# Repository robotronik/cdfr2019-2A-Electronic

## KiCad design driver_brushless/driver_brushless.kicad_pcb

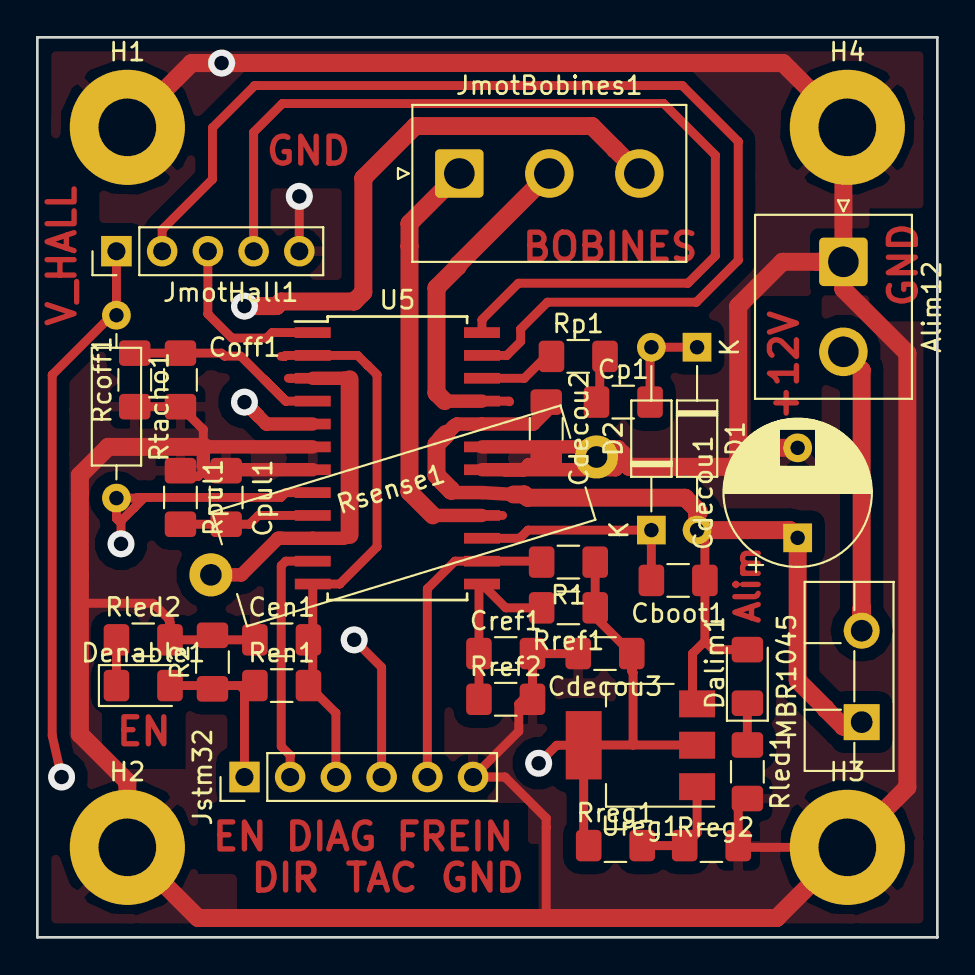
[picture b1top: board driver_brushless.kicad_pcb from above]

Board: 2 copper layers, 50.0 x 50.0 mm, 38 parts (0 on the bottom side), 26 nets.

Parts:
Alim12: B_Plug_5mm; JST_NV_B02P-NV_1x02_P5.00mm_Vertical
Cboot1: 220n; C_1206_3216Metric_Pad1.42x1.75mm_HandSolder
Cdecou1: 100µF; CP_Radial_D8.0mm_P5.00mm
Cdecou2, Cdecou3: 100nF; C_1206_3216Metric_Pad1.42x1.75mm_HandSolder
Cen1: 5.6n; C_1206_3216Metric_Pad1.42x1.75mm_HandSolder
Coff1: 1n; C_1206_3216Metric_Pad1.42x1.75mm_HandSolder
Cp1: 10n; C_1206_3216Metric_Pad1.42x1.75mm_HandSolder
Cpul1: 10n; C_1206_3216Metric_Pad1.42x1.75mm_HandSolder
Cref1: 10n; C_1206_3216Metric_Pad1.42x1.75mm_HandSolder
D1, D2: 1N4148; D_DO-35_SOD27_P10.16mm_Horizontal
Dalim1: LED; LED_1206_3216Metric_Pad1.42x1.75mm_HandSolder
Denable1: LED; LED_1206_3216Metric_Pad1.42x1.75mm_HandSolder
H1, H2, H3, H4: MountingHole_Pad; MountingHole_3.2mm_M3_Pad
JmotBobines1: Conn_01x03_Female; JST_NV_B03P-NV_1x03_P5.00mm_Vertical
JmotHall1: Conn_01x05_Female; PinHeader_1x05_P2.54mm_Vertical
Jstm32: Conn_01x06_Male; PinHeader_1x06_P2.54mm_Vertical
MBR1045: D_Schottky; TO-220F-2_Vertical
R1, R2: 100k; R_1206_3216Metric_Pad1.42x1.75mm_HandSolder
Rcoff1: 33k; R_1206_3216Metric_Pad1.42x1.75mm_HandSolder
Ren1: 100k; R_1206_3216Metric_Pad1.42x1.75mm_HandSolder
Rled1: 2,2k; R_1206_3216Metric_Pad1.42x1.75mm_HandSolder
Rled2: 680; R_1206_3216Metric_Pad1.42x1.75mm_HandSolder
Rp1: 100; R_1206_3216Metric_Pad1.42x1.75mm_HandSolder
Rpul1: 47k; R_1206_3216Metric_Pad1.42x1.75mm_HandSolder
Rref1: 1.2k; R_1206_3216Metric_Pad1.42x1.75mm_HandSolder
Rref2: 220; R_1206_3216Metric_Pad1.42x1.75mm_HandSolder
Rreg1: 270; R_1206_3216Metric_Pad1.42x1.75mm_HandSolder
Rreg2: 820; R_1206_3216Metric_Pad1.42x1.75mm_HandSolder
Rsense1: 0.3; R_Axial_Power_L20.0mm_W6.4mm_P22.40mm
Rtacho1: 1k; R_Axial_DIN0207_L6.3mm_D2.5mm_P10.16mm_Horizontal
U5: L6235D; SOIC-24W_7.5x15.4mm_P1.27mm
Ureg1: LM317; SOT-223-3_TabPin2

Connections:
+5V: Cdecou3.1, JmotHall1.1, R1.1, Rref1.1, Rreg1.1, Rtacho1.1, Ureg1.2
+12V: Cboot1.1, Cdecou1.1, Cdecou2.1, D1.2, Dalim1.2, MBR1045.1, U5.17, U5.20, Ureg1.3
/Hall_sensor_11: JmotHall1.3, U5.1
/Hall_sensor_21: JmotHall1.2, U5.23
/Hall_sensor_31: JmotHall1.4, U5.24
/Out_11: JmotBobines1.3, U5.5
/Out_21: JmotBobines1.2, U5.21
/Out_31: JmotBobines1.1, U5.16
GND: Alim12.1, Cdecou1.2, Cdecou2.2, Cdecou3.2, Cen1.1, Coff1.1, Cpul1.1, Cref1.2, H1.1, H2.1, H3.1, H4.1, JmotHall1.5, Jstm32.6, R2.2, Rcoff1.1, Rled1.2, Rled2.2, Rpul1.1, Rref2.2, Rreg2.2, Rsense1.2, U5.6, U5.7, U5.18, U5.19
unnamed: Alim12.2, MBR1045.2
unnamed: Cboot1.2, D2.1, U5.15
unnamed: Cen1.2, Jstm32.3, Ren1.2, U5.2, U5.12
unnamed: Coff1.2, Rcoff1.2, U5.4
unnamed: Cp1.1, Rp1.2
unnamed: Cp1.2, D1.1, D2.2
unnamed: Cpul1.2, Rpul1.2, U5.9
unnamed: Cref1.1, Rref1.2, Rref2.1, U5.13
unnamed: Dalim1.1, Rled1.1
unnamed: Denable1.1, Rled2.1
unnamed: Denable1.2, Jstm32.1, R2.1, Ren1.1
unnamed: Jstm32.2, U5.11
unnamed: Jstm32.4, Rtacho1.2, U5.8
unnamed: Jstm32.5, R1.2, U5.14
unnamed: Rp1.1, U5.22
unnamed: Rreg1.2, Rreg2.1, Ureg1.1
unnamed: Rsense1.1, U5.3, U5.10

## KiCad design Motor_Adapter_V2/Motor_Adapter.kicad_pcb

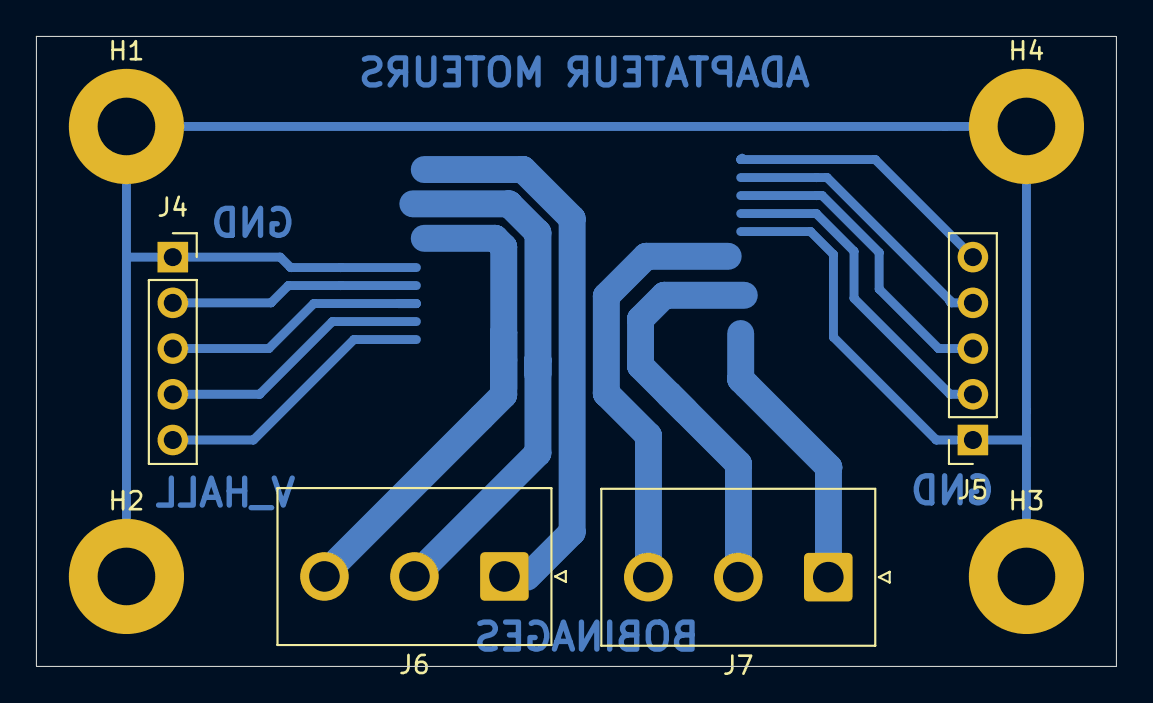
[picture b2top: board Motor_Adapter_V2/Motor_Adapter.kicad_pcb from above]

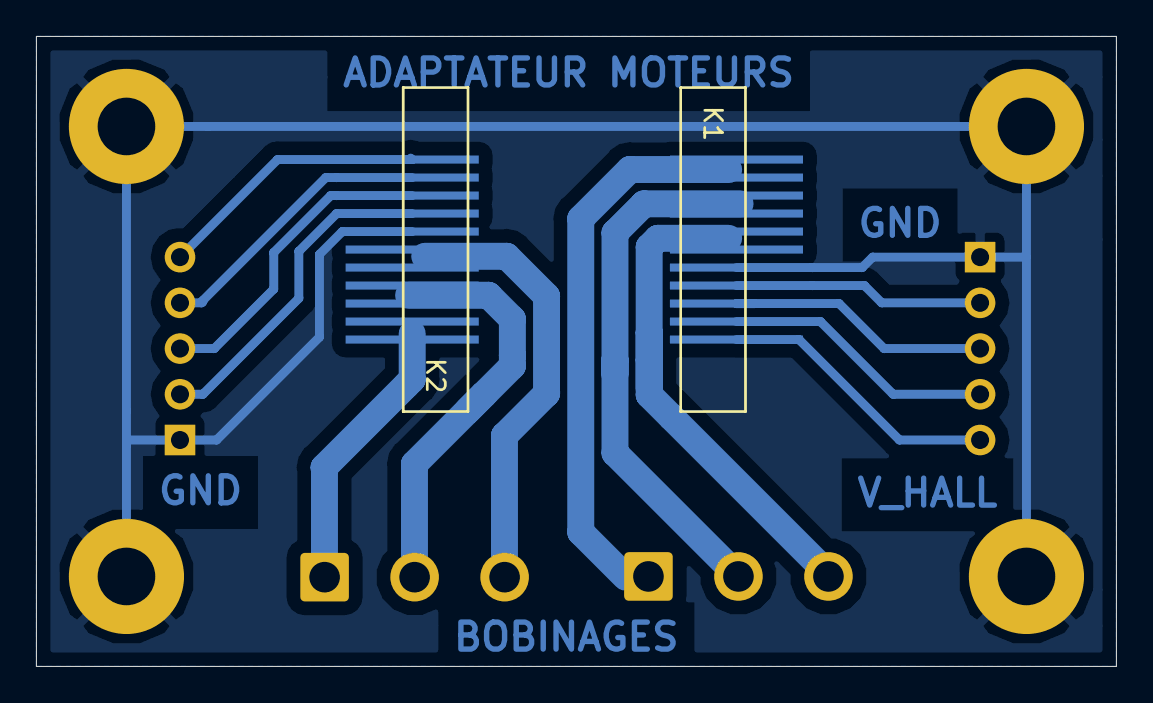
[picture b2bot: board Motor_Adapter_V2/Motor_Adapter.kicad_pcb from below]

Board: 2 copper layers, 60.0 x 35.0 mm, 10 parts (2 on the bottom side), 15 nets.

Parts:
H1, H2, H3, H4: MountingHole_Pad; MountingHole_3.2mm_M3_Pad
J4, J5: Hall_Sensor; PinSocket_1x05_P2.54mm_Vertical
J6, J7: Conn_01x03_Female; JST_NV_B03P-NV_1x03_P5.00mm_Vertical
K1, K2: Maxon-200142; Molex-52610-1133

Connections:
GND: H1.1, H2.1, H3.1, H4.1, J4.1, J5.1, K1.7, K2.7
unnamed: J4.2, K1.8
unnamed: J4.3, K1.9
unnamed: J4.4, K1.10
unnamed: J4.5, K1.11
unnamed: J5.2, K2.8
unnamed: J5.3, K2.9
unnamed: J5.4, K2.10
unnamed: J5.5, K2.11
unnamed: J6.1, K1.1, K1.2
unnamed: J6.2, K1.3, K1.4
unnamed: J6.3, K1.5, K1.6
unnamed: J7.1, K2.1, K2.2
unnamed: J7.2, K2.3, K2.4
unnamed: J7.3, K2.5, K2.6

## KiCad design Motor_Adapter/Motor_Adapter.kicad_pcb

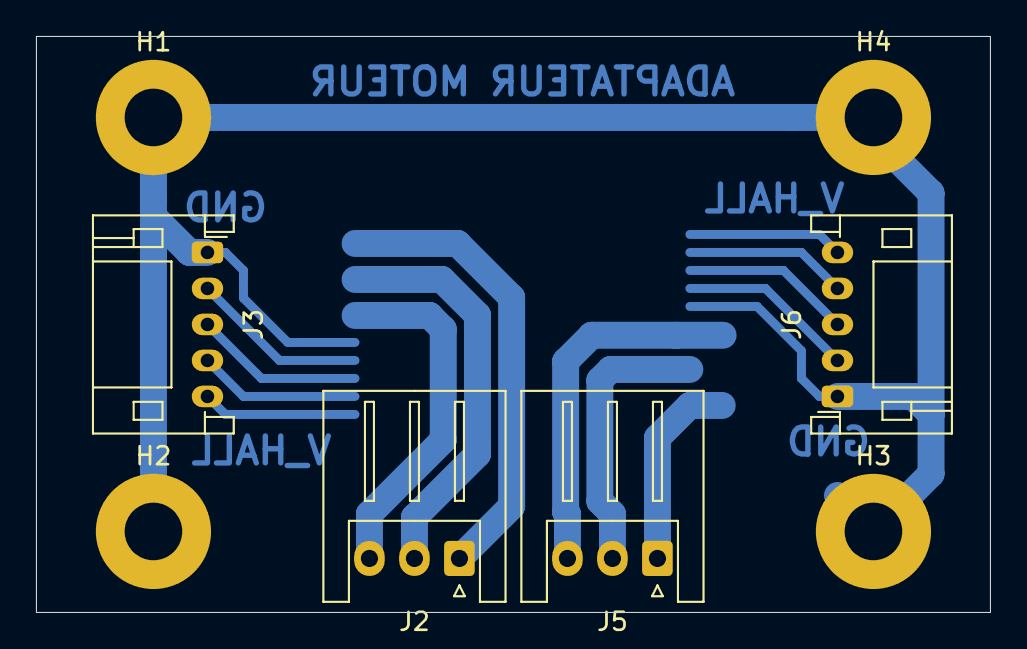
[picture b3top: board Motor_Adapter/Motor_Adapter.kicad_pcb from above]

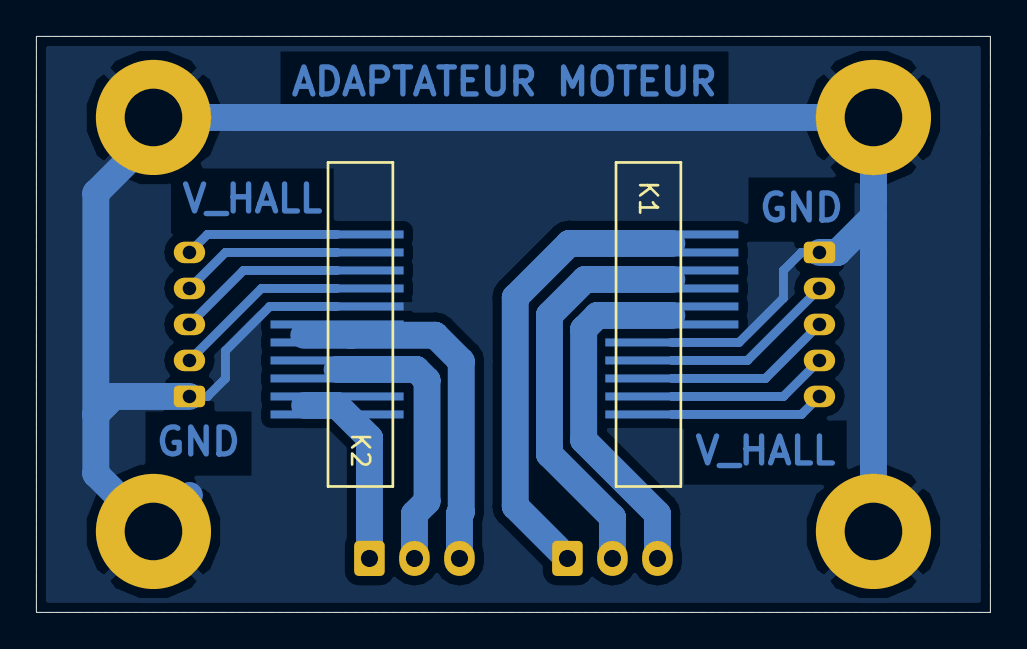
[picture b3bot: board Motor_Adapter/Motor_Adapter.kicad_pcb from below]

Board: 2 copper layers, 53.0 x 32.0 mm, 10 parts (2 on the bottom side), 15 nets.

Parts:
H1, H2, H3, H4: MountingHole_Pad; MountingHole_3.2mm_M3_Pad
J2, J5: Windings; JST_XH_S3B-XH-A_1x03_P2.50mm_Horizontal
J3, J6: Hall_Sensor; JST_PH_S5B-PH-K_1x05_P2.00mm_Horizontal
K1, K2: Maxon-200142; Molex-52610-1133

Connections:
GND: H1.1, H2.1, H3.1, H4.1, J3.1, J6.1, K1.7, K2.7
unnamed: J2.1, K1.1, K1.2
unnamed: J2.2, K1.3, K1.4
unnamed: J2.3, K1.5, K1.6
unnamed: J3.2, K1.8
unnamed: J3.3, K1.9
unnamed: J3.4, K1.10
unnamed: J3.5, K1.11
unnamed: J5.1, K2.1, K2.2
unnamed: J5.2, K2.3, K2.4
unnamed: J5.3, K2.5, K2.6
unnamed: J6.2, K2.8
unnamed: J6.3, K2.9
unnamed: J6.4, K2.10
unnamed: J6.5, K2.11

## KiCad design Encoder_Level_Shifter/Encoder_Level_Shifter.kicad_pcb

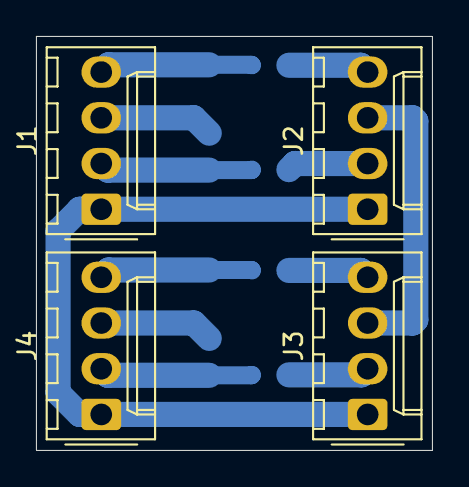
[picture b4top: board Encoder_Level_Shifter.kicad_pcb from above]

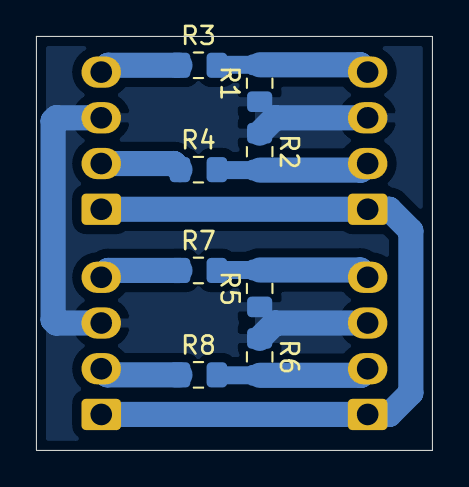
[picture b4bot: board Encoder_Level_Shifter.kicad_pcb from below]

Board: 2 copper layers, 22.0 x 23.0 mm, 12 parts (8 on the bottom side), 10 nets.

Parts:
J1, J2, J3, J4: Conn_01x04; Molex_KK-254_AE-6410-04A_1x04_P2.54mm_Vertical
R1, R2, R5, R6: 10k; R_0805_2012Metric_Pad1.15x1.40mm_HandSolder
R3, R4, R7, R8: 5.4k; R_0805_2012Metric_Pad1.15x1.40mm_HandSolder

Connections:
+5V: J1.1, J2.1, J3.1, J4.1
GND: J1.3, J2.3, J3.3, J4.3, R1.1, R2.1, R5.1, R6.1
unnamed: J1.2, R2.2, R4.2
unnamed: J1.4, R1.2, R3.2
unnamed: J2.2, R4.1
unnamed: J2.4, R3.1
unnamed: J3.2, R8.1
unnamed: J3.4, R7.1
unnamed: J4.2, R6.2, R8.2
unnamed: J4.4, R5.2, R7.2

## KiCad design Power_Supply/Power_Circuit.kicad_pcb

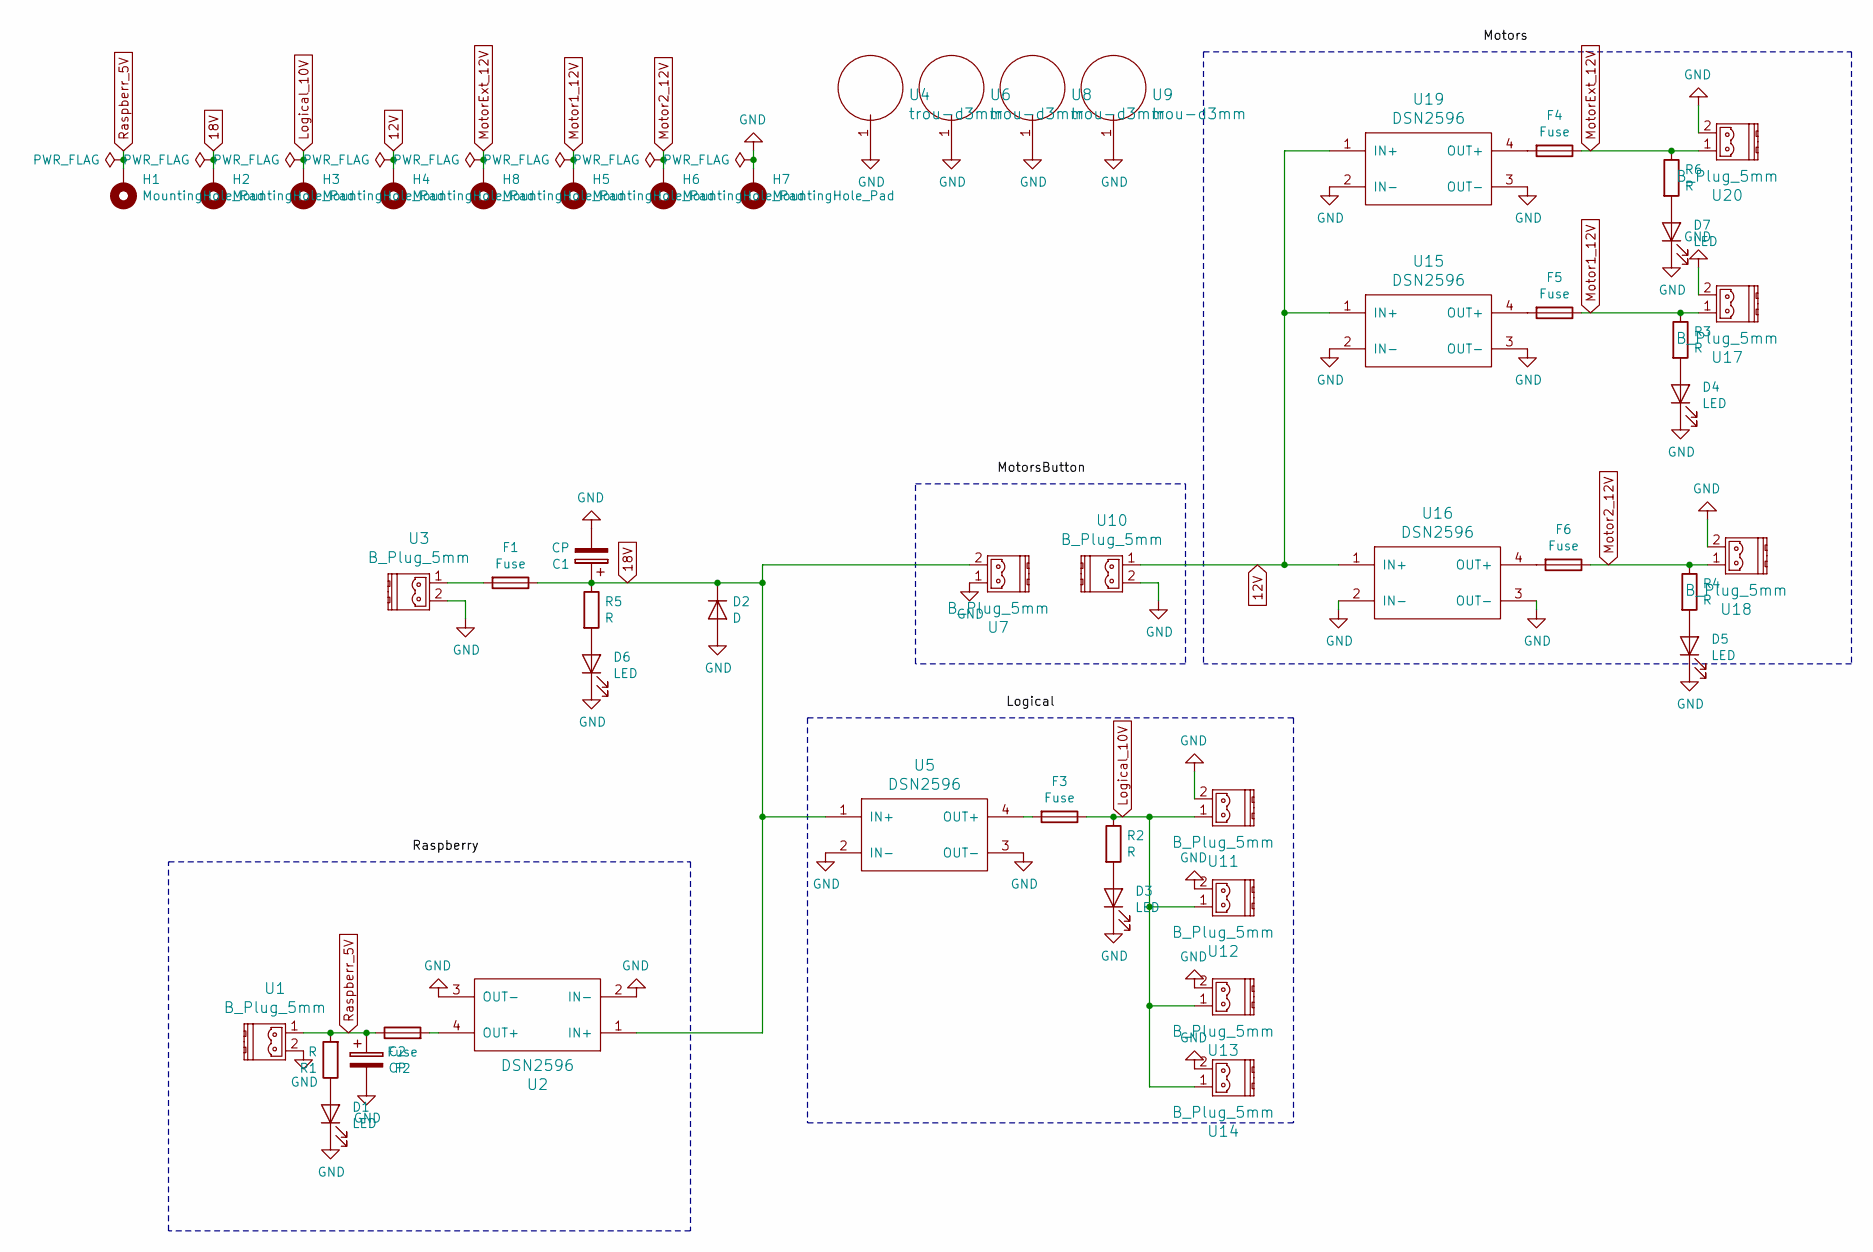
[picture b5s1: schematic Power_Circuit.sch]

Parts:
C1, C2: CP; CP_Radial_D8.0mm_P3.50mm
D1, D3, D4, D5, D6, D7: LED; LED_1206_3216Metric_Pad1.42x1.75mm_HandSolder
D2: D; D_DO-35_SOD27_P10.16mm_Horizontal
F1, F2, F3, F4, F5, F6: Fuse; Fuse_1206_3216Metric_Pad1.42x1.75mm_HandSolder
H1, H2, H3, H4, H5, H6, H7, H8: MountingHole_Pad; PinHeader_1x01_P1.00mm_Horizontal
R1, R2, R3, R4, R5, R6: R; R_1206_3216Metric_Pad1.42x1.75mm_HandSolder
U1, U3, U7, U10, U11, U12, U13, U14, U17, U18, U20: B_Plug_5mm; B plug 5mm
U2, U5, U15, U16, U19: DSN2596
U4, U6, U8, U9: trou-d3mm; trou_d3mm

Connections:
12V: H4.1, U10.1, U15.1 (IN+), U16.1 (IN+), U19.1 (IN+)
18V: C1.1, D2.1 (K), F1.1, H2.1, R5.1, U2.1 (IN+), U5.1 (IN+), U7.2
GND: C1.2, C2.2, D1.1 (K), D2.2 (A), D3.1 (K), D4.1 (K), D5.1 (K), D6.1 (K), D7.1 (K), H7.1, U1.2, U2.2 (IN-), U2.3 (OUT-), U3.2, U4.1, U5.2 (IN-), U5.3 (OUT-), U6.1, U7.1, U8.1, U9.1, U10.2, U11.2, U12.2, U13.2, U14.2, U15.2 (IN-), U15.3 (OUT-), U16.2 (IN-), U16.3 (OUT-), U17.2, U18.2, U19.2 (IN-), U19.3 (OUT-), U20.2
Logical_10V: F3.1, H3.1, R2.1, U11.1, U12.1, U13.1, U14.1
Motor1_12V: F5.1, H5.1, R3.1, U17.1
Motor2_12V: F6.1, H6.1, R4.1, U18.1
MotorExt_12V: F4.1, H8.1, R6.1, U20.1
unnamed: D1.2 (A), R1.1
unnamed: D3.2 (A), R2.2
unnamed: D4.2 (A), R3.2
unnamed: D5.2 (A), R4.2
unnamed: D6.2 (A), R5.2
unnamed: D7.2 (A), R6.2
unnamed: F1.2, U3.1
unnamed: F2.2, U2.4 (OUT+)
unnamed: F3.2, U5.4 (OUT+)
unnamed: F4.2, U19.4 (OUT+)
unnamed: F5.2, U15.4 (OUT+)
unnamed: F6.2, U16.4 (OUT+)
Raspberr_5V: C2.1, F2.1, H1.1, R1.2, U1.1

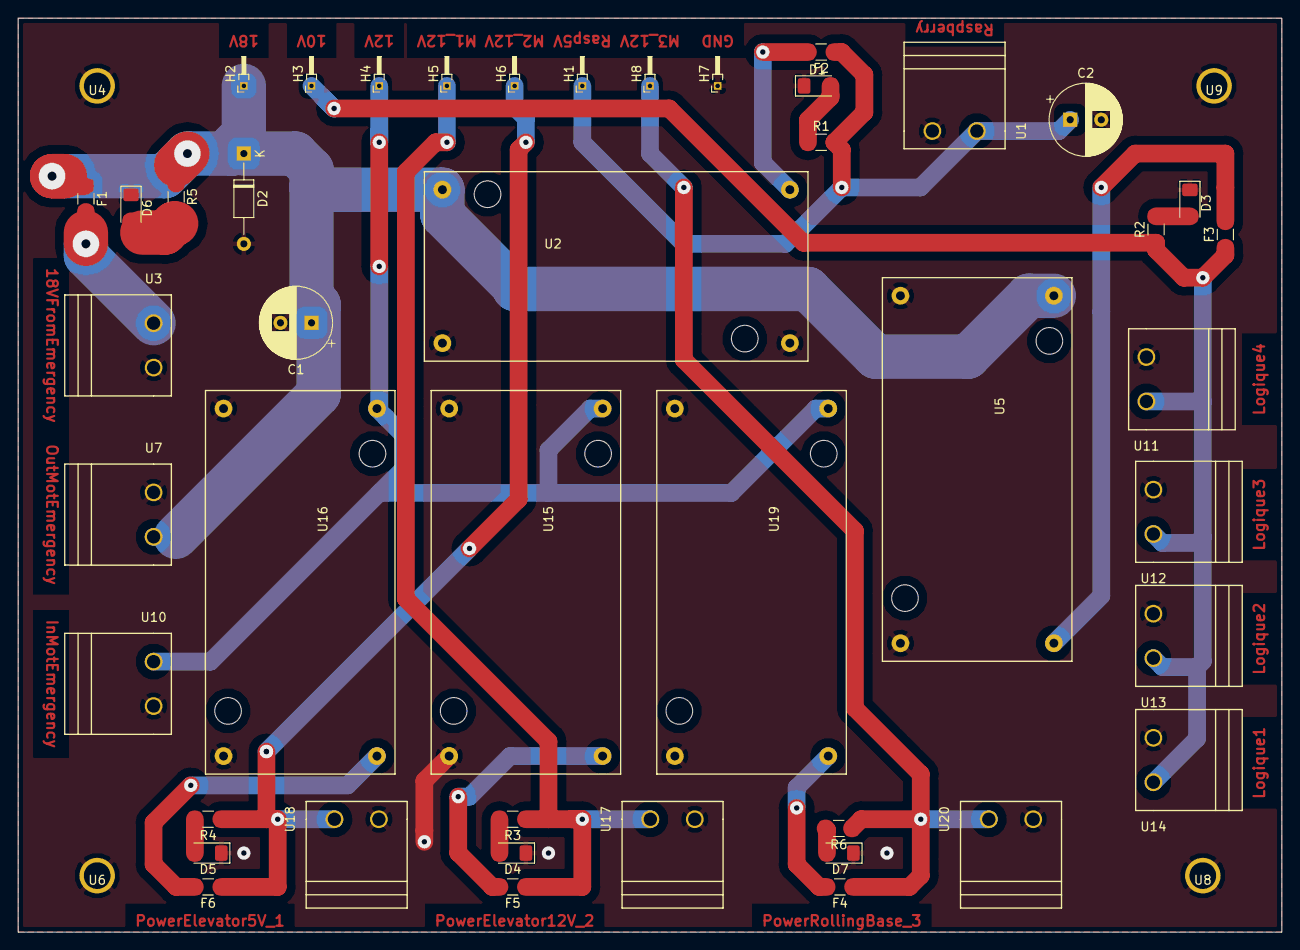
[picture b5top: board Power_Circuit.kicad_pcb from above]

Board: 2 copper layers, 142.2 x 102.9 mm, 49 parts (0 on the bottom side), 20 nets.

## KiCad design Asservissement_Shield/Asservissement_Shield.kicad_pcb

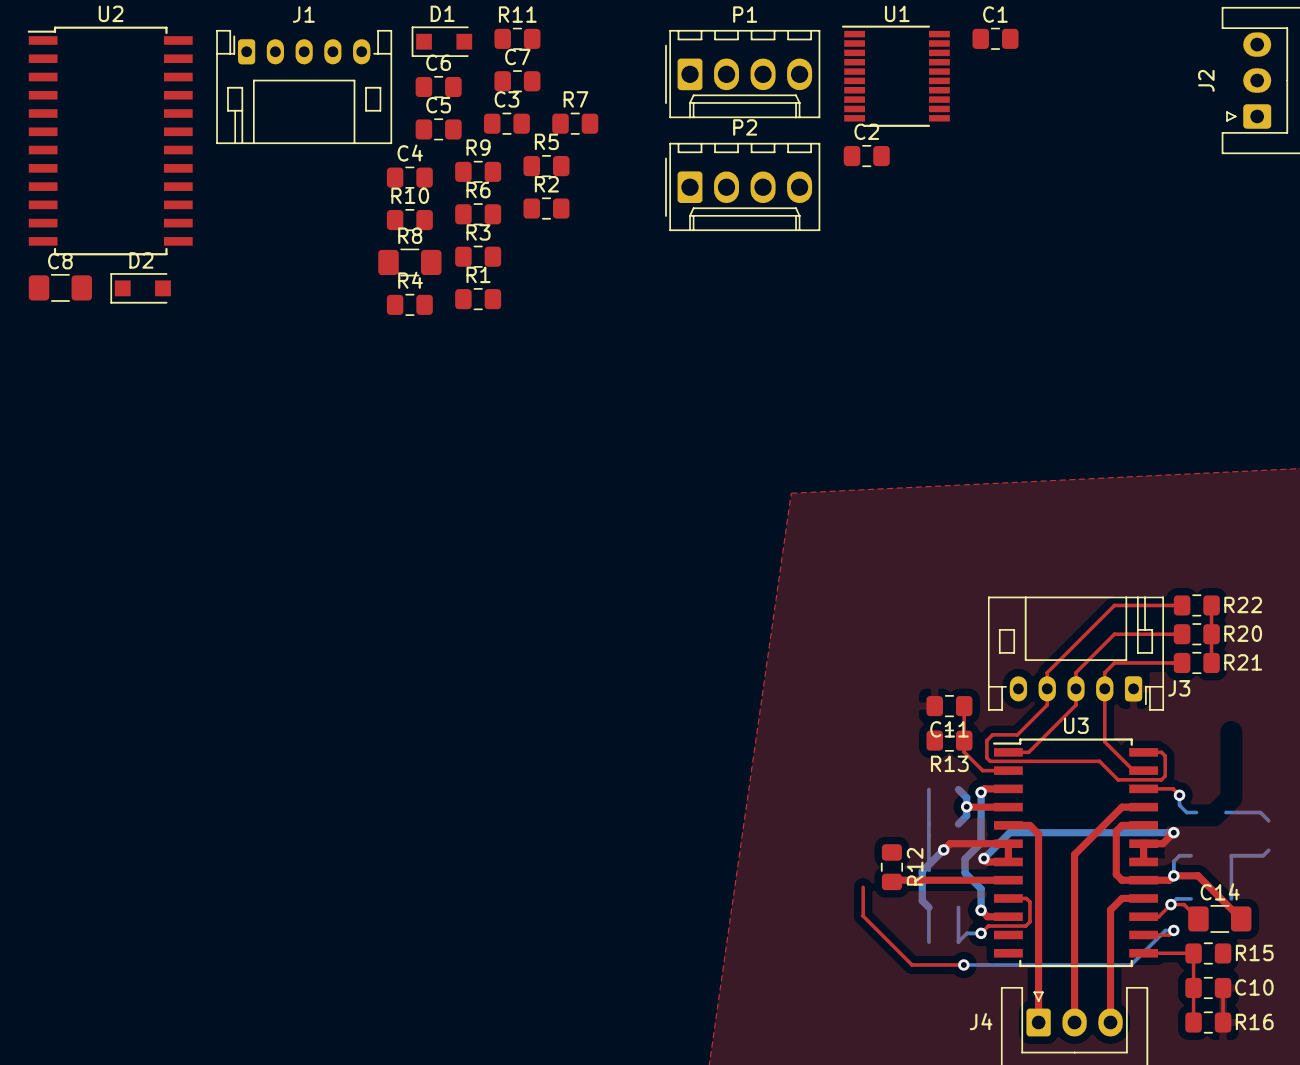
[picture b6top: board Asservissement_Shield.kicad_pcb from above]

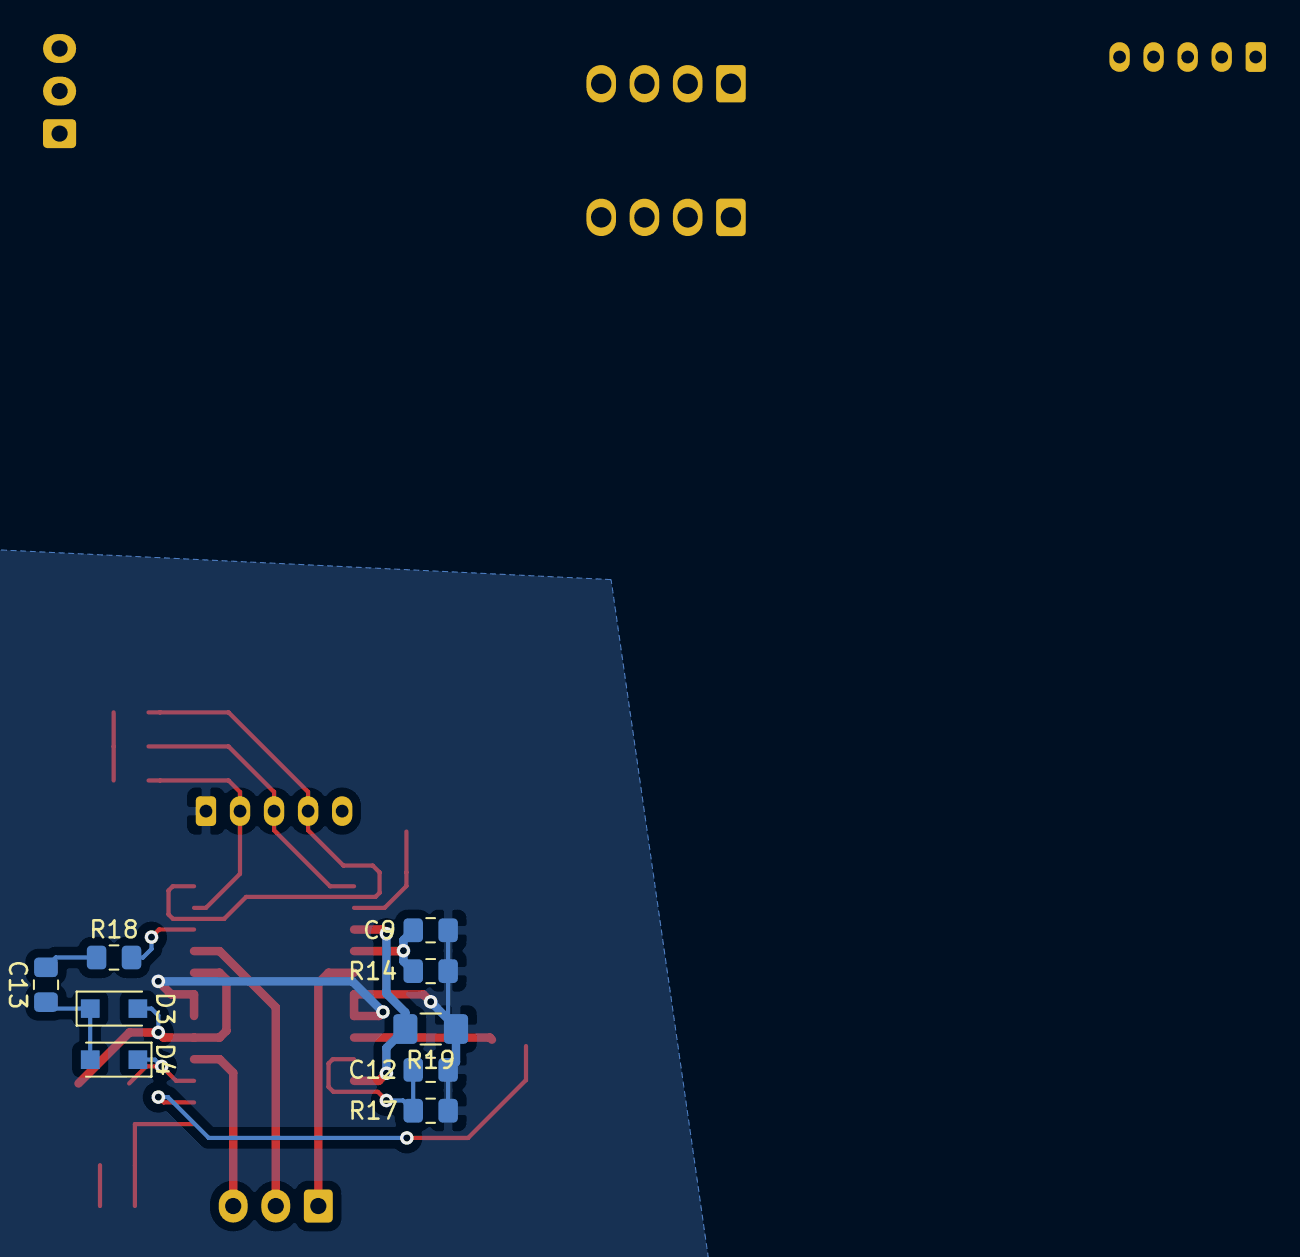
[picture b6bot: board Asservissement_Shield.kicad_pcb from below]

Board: 2 copper layers, 49 parts (9 on the bottom side), 40 nets.

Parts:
C1, C2: 100n; C_0805_2012Metric_Pad1.15x1.40mm_HandSolder
C3, C6, C9, C12: 1n; C_0805_2012Metric_Pad1.15x1.40mm_HandSolder
C4, C7, C10, C13: 10n; C_0805_2012Metric_Pad1.15x1.40mm_HandSolder
C5, C11: 5.6n; C_0805_2012Metric_Pad1.15x1.40mm_HandSolder
C8, C14: 220n; C_1206_3216Metric_Pad1.42x1.75mm_HandSolder
D1, D2, D3, D4: 1N4148; D_SOD-123F
J1, J3: Hall_Sensor; JST_PH_S5B-PH-K_1x05_P2.00mm_Horizontal
J2, J4: Windings; JST_XH_S3B-XH-A_1x03_P2.50mm_Horizontal
P1, P2: encoder_2; Molex_KK-254_AE-6410-04A_1x04_P2.54mm_Vertical
R1, R12: 1k; R_0805_2012Metric_Pad1.15x1.40mm_HandSolder
R2, R13: 100k; R_0805_2012Metric_Pad1.15x1.40mm_HandSolder
R3, R14: 35k; R_0805_2012Metric_Pad1.15x1.40mm_HandSolder
R4, R15: 1k2; R_0805_2012Metric_Pad1.15x1.40mm_HandSolder
R5, R16: 220; R_0805_2012Metric_Pad1.15x1.40mm_HandSolder
R6, R17: 47k; R_0805_2012Metric_Pad1.15x1.40mm_HandSolder
R7, R18: 100; R_0805_2012Metric_Pad1.15x1.40mm_HandSolder
R8, R19: 0.3; R_1206_3216Metric_Pad1.42x1.75mm_HandSolder
R9, R10, R11, R20, R21, R22: 0; R_0805_2012Metric_Pad1.15x1.40mm_HandSolder
U1: TXS0108EPW; TSSOP-20_4.4x6.5mm_P0.65mm
U2, U3: L6235PD; SOIC-24W_7.5x15.4mm_P1.27mm

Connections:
+3V3: C1.1, R1.1, R4.1, R12.1, R15.1, U1.2, U1.10
+5V: C2.1, P1.1, P2.1, R9.1, R10.1, R11.1, R20.1, R21.1, R22.1, U1.19
/Diagnostic_1: C11.1, R13.1, U3.2, U3.12
/Diagnostic_2: C5.1, R2.1, U2.2, U2.12
/Encoders/Ch_A1(+5V): P1.2, U1.15
/Encoders/Ch_A2(+5V): P2.2, U1.13
/Encoders/Ch_B1(+5V): P1.4, U1.14
/Encoders/Ch_B2(+5V): P2.4, U1.12
/MotorA/Hall_Sensor1: J1.3, R9.2, U2.1
/MotorA/Hall_Sensor2: J1.2, R10.2, U2.23
/MotorA/Hall_Sensor3: J1.4, R11.2, U2.24
/MotorA/Motor_Winding1: J2.1, U2.5
/MotorA/Motor_Winding2: J2.2, U2.21
/MotorA/Motor_Winding3: J2.3, U2.16
/MotorB/Hall_Sensor1: J3.3, R20.2, U3.1
/MotorB/Hall_Sensor2: J3.2, R21.2, U3.23
/MotorB/Hall_Sensor3: J3.4, R22.2, U3.24
/MotorB/Motor_Winding1: J4.1, U3.5
/MotorB/Motor_Winding2: J4.2, U3.21
/MotorB/Motor_Winding3: J4.3, U3.16
/Tachometer_1: R12.2, U3.8
/Tachometer_2: R1.2, U2.8
GND: C1.2, C2.2, C3.2, C4.2, C5.2, C6.2, C9.2, C10.2, C11.2, C12.2, J1.1, J3.1, P1.3, P2.3, R3.2, R5.2, R6.2, R8.1, R14.2, R16.2, R17.2, R19.1, U1.11, U2.6, U2.7, U2.18, U2.19, U3.6, U3.7, U3.18, U3.19
unnamed: C3.1, R3.1, U2.4
unnamed: C4.1, R4.2, R5.1, U2.13
unnamed: C6.1, R6.1, U2.9
unnamed: C7.1, D1.1, D2.2
unnamed: C7.2, R7.1
unnamed: C8.1, D2.1, U2.15
unnamed: C9.1, R14.1, U3.4
unnamed: C10.1, R15.2, R16.1, U3.13
unnamed: C12.1, R17.1, U3.9
unnamed: C13.1, D3.1, D4.2
unnamed: C13.2, R18.1
unnamed: C14.1, D4.1, U3.15
unnamed: R7.2, U2.22
unnamed: R8.2, U2.3, U2.10
unnamed: R18.2, U3.22
unnamed: R19.2, U3.3, U3.10
VCC: C8.2, C14.2, D1.2, D3.2, U2.17, U2.20, U3.17, U3.20

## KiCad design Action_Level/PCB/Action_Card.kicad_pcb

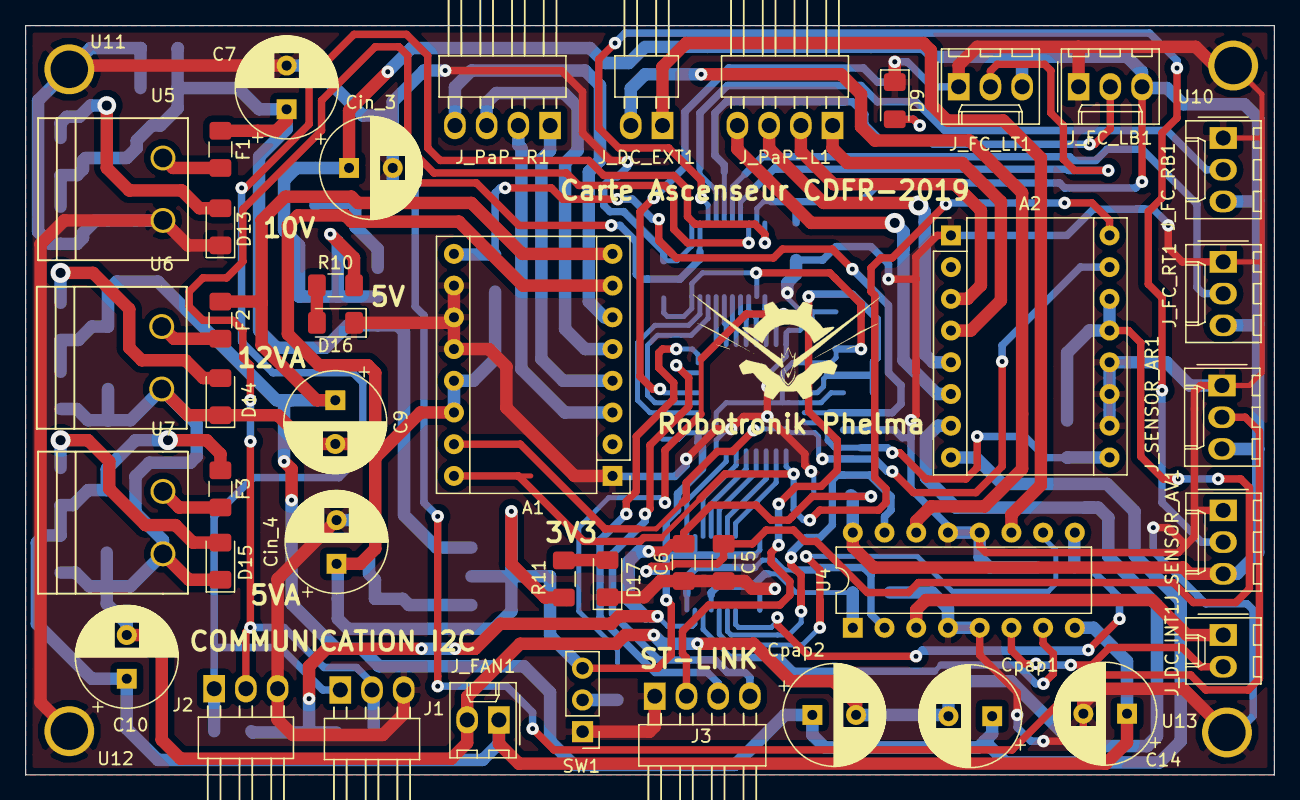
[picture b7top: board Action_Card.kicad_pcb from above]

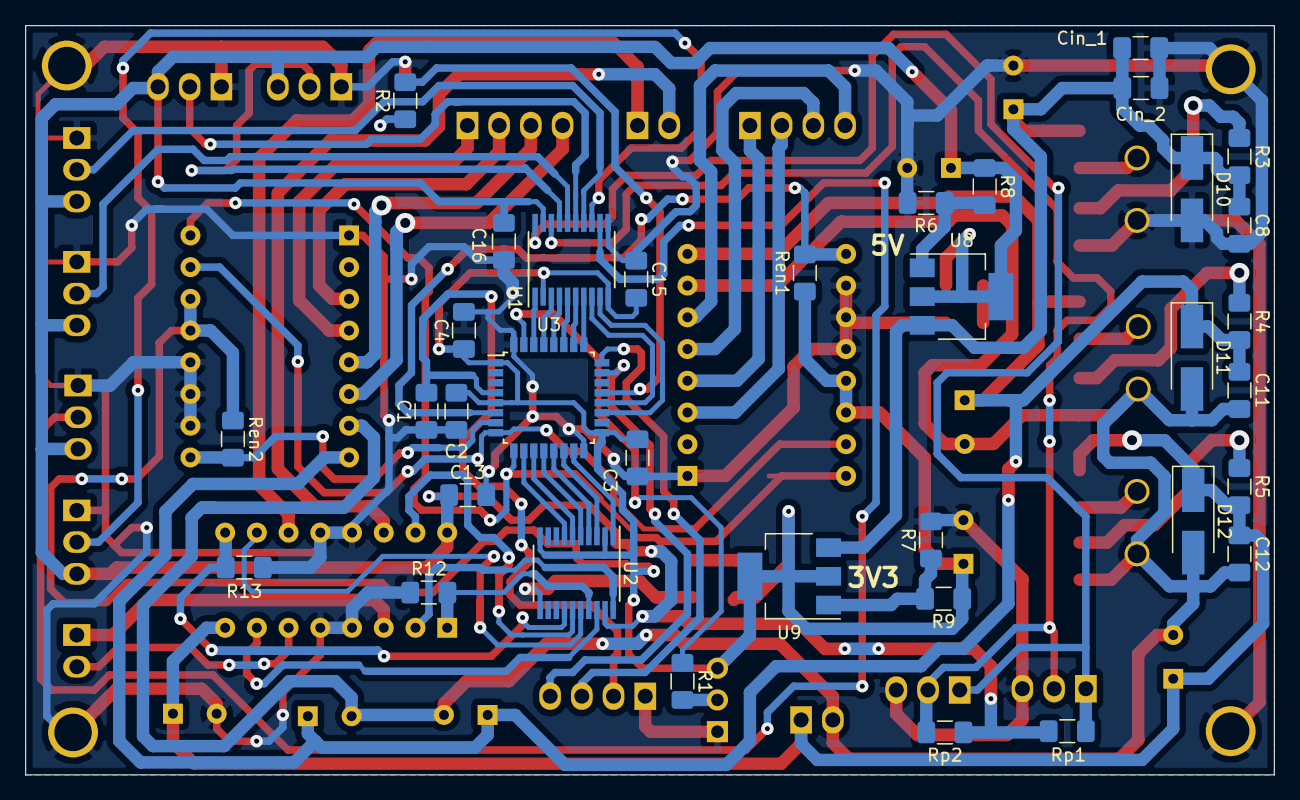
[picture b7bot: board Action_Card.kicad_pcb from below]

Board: 2 copper layers, 100.0 x 60.0 mm, 81 parts (35 on the bottom side), 68 nets.

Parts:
A1, A2: Pololu_Breakout_DRV8825; Pololu_Breakout-16_15.2x20.3mm
C1, C2, C3, C4, C8, C11, C12: 100n; C_1206_3216Metric_Pad1.42x1.75mm_HandSolder
C5, C6, C13, C15, C16: 0.1u; C_1206_3216Metric_Pad1.42x1.75mm_HandSolder
C7, C9, C10: 100u; CP_Radial_D8.0mm_P3.50mm
C14: 1u; CP_Radial_D8.0mm_P3.50mm
Cin_1, Cin_2: 0,1u; C_1206_3216Metric_Pad1.42x1.75mm_HandSolder
Cin_3, Cin_4: 10u; CP_Radial_D8.0mm_P3.50mm
Cpap1, Cpap2: 100uF; CP_Radial_D8.0mm_P3.50mm
D9: LED_STM; LED_1206_3216Metric_Pad1.42x1.75mm_HandSolder
D10, D11, D12: D_10A; D_SMA_Handsoldering
D13: LED_ALT; LED_1206_3216Metric_Pad1.42x1.75mm_HandSolder
D14: LED_PaP; LED_1206_3216Metric_Pad1.42x1.75mm_HandSolder
D15: LED_DC; LED_1206_3216Metric_Pad1.42x1.75mm_HandSolder
D16: LED_5V; LED_1206_3216Metric_Pad1.42x1.75mm_HandSolder
D17: LED_3V3; LED_1206_3216Metric_Pad1.42x1.75mm_HandSolder
F1: Fuse_Num; Fuse_1206_3216Metric_Pad1.42x1.75mm_HandSolder
F2, F3: Fuse_Pwr; Fuse_1206_3216Metric_Pad1.42x1.75mm_HandSolder
J1, J2: Conn_01x03; Molex_KK-254_1x03_P2.54mm_Horizontal
J3: Conn_01x04; Molex_KK-254_1x04_P2.54mm_Horizontal
J_DC_EXT1: Conn_MDC; Molex_KK-254_1x02_P2.54mm_Horizontal
J_DC_INT1: Conn_MDC; Molex_KK-254_AE-6410-02A_1x02_P2.54mm_Vertical
J_FAN1: Conn_01x02; Molex_KK-254_AE-6410-02A_1x02_P2.54mm_Vertical
J_FC_LB1: Conn_01x02; Molex_KK-254_AE-6410-03A_1x03_P2.54mm_Vertical
J_FC_LT1: Conn_01x02; Molex_KK-254_AE-6410-03A_1x03_P2.54mm_Vertical
J_FC_RB1: Conn_01x02; Molex_KK-254_AE-6410-03A_1x03_P2.54mm_Vertical
J_FC_RT1: Conn_01x02; Molex_KK-254_AE-6410-03A_1x03_P2.54mm_Vertical
J_PaP-L1: Conn_01x04; Molex_KK-254_1x04_P2.54mm_Horizontal
J_PaP-R1: Conn_01x04; Molex_KK-254_1x04_P2.54mm_Horizontal
J_SENSOR_AR1: Conn_01x04; Molex_KK-254_AE-6410-03A_1x03_P2.54mm_Vertical
J_SENSOR_AV1: Conn_01x04; Molex_KK-254_AE-6410-03A_1x03_P2.54mm_Vertical
R1, R12, R13: 10k; R_1206_3216Metric_Pad1.42x1.75mm_HandSolder
R2, R10, R11: 470; R_1206_3216Metric_Pad1.42x1.75mm_HandSolder
R3, R4, R5: 2k; R_1206_3216Metric_Pad1.42x1.75mm_HandSolder
R6: 820; R_1206_3216Metric_Pad1.42x1.75mm_HandSolder
R7: 370; R_1206_3216Metric_Pad1.42x1.75mm_HandSolder
R8: 270; R_1206_3216Metric_Pad1.42x1.75mm_HandSolder
R9: 220; R_1206_3216Metric_Pad1.42x1.75mm_HandSolder
Ren1, Ren2: 10k; R_1206_3216Metric_Pad1.42x1.75mm_HandSolder
Rp1, Rp2: 10k; R_1206_3216Metric_Pad1.42x1.75mm_HandSolder
SW1: SW_DPDT_x2; PinHeader_1x03_P2.54mm_Vertical
U1, U2: txb0108; TSSOP-20_4.4x6.5mm_P0.65mm
U3: stm32f042k6tx; LQFP-32_7x7mm_P0.8mm
U4: L293; DIP-16_W7.62mm
U5, U6, U7: B_Plug_5mm; Bplug-5mm
U8, U9: LM317_SOT223; SOT-223-3_TabPin2
U10, U11, U12, U13: Trou-3

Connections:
+3V3: A1.13, A1.14, A2.13, A2.14, C2.2, C3.1, C4.1, C5.1, C15.1, Cin_4.1, R9.1, R11.2, Ren1.1, Ren2.1, SW1.3, U1.2, U1.10, U2.2, U2.10, U3.1, U3.5, U3.17, U9.2
+5V: C6.1, C13.1, C16.1, Cin_3.1, J_FC_LB1.3, J_FC_LT1.3, J_FC_RB1.3, J_FC_RT1.3, J_SENSOR_AR1.3, J_SENSOR_AV1.3, R8.1, R10.2, Rp1.1, Rp2.1, U1.19, U2.19, U4.16, U8.2
+5VA: C10.1, C12.1, C14.1, D12.1, F3.1, J_FAN1.1, R5.2, U4.8
+10V: C7.1, C8.1, Cin_1.1, Cin_2.1, D10.1, F1.1, R3.2, U8.3, U9.3
+12VA: A1.8, A2.8, C9.1, C11.1, Cpap1.1, Cpap2.1, D11.1, F2.1, R4.2
/Communication-Part/SCL(3V3): U1.3, U3.29
/Communication-Part/SCL(5V): J1.2, J2.2, Rp2.2, U1.18
/Communication-Part/SDA(3V3): U1.1, U3.30
/Communication-Part/SDA(5V): J1.1, J2.1, Rp1.2, U1.20
/Communication-Part/nrst(3V3): C1.1, J3.2, U3.4
/Communication-Part/swclk(3V3): J3.3, U3.24
/Communication-Part/swdio(3V3): J3.4, U3.23
/Controller-Part/DIR_PaP: A1.16, A2.16, U3.9
/Controller-Part/EN_DC_EXT: R13.1, U2.14, U4.9
/Controller-Part/EN_DC_EXT(3V3): U2.7, U3.10
/Controller-Part/EN_DC_INT: R12.1, U2.17, U4.1
/Controller-Part/EN_DC_INT(3V3): U2.4, U3.13
/Controller-Part/FC_LB: U1.6, U3.26
/Controller-Part/FC_LT: U1.4, U3.28
/Controller-Part/FC_RB: U1.7, U3.25
/Controller-Part/FC_RT: U1.5, U3.27
/Controller-Part/PWM_L-DC_EXT: U2.16, U4.10
/Controller-Part/PWM_L-DC_EXT(3V3): U2.5, U3.12
/Controller-Part/PWM_L-DC_INT: U2.20, U4.2
/Controller-Part/PWM_L-DC_INT(3V3): U2.1, U3.15
/Controller-Part/PWM_R-DC_EXT: U2.15, U4.15
/Controller-Part/PWM_R-DC_EXT(3V3): U2.6, U3.11
/Controller-Part/PWM_R-DC_INT: U2.18, U4.7
/Controller-Part/PWM_R-DC_INT(3V3): U2.3, U3.14
/Controller-Part/SENSOR_AR: U1.9, U3.19
/Controller-Part/SENSOR_AV: U1.8, U3.20
/Controller-Part/STEP_PaP: A1.15, A2.15, U3.8
/Controller-Part/~EN~_PaP-L: A2.9, Ren2.2, U3.7
/Controller-Part/~EN~_PaP-R: A1.9, Ren1.2, U3.6
/Power-Part/Alim_Puiss_DC: F3.2, U7.1
/Power-Part/Alim_Puiss_PaP: F2.2, U6.1
/Power-Part/Alim_num: F1.2, U5.1
GND: A1.1, A1.10, A1.11, A1.12, A2.1, A2.10, A2.11, A2.12, C1.2, C2.1, C3.2, C4.2, C5.2, C6.2, C7.2, C8.2, C13.2, C14.2, C15.2, C16.2, Cin_1.2, Cin_2.2, Cin_3.2, Cin_4.2, D9.1, D10.2, D13.1, D16.1, D17.1, J1.3, J2.3, J3.1, J_FC_LB1.1, J_FC_LT1.1, J_FC_RB1.1, J_FC_RT1.1, J_SENSOR_AR1.1, J_SENSOR_AV1.1, R6.2, R7.2, R12.2, R13.2, SW1.1, U1.11, U2.11, U3.16, U3.32, U4.4, U4.5, U4.12, U4.13, U5.2, U10.1, U11.1, U12.1, U13.1
GNDPWR: A1.7, A2.7, C9.2, C10.2, C11.2, C12.2, Cpap1.2, Cpap2.2, D11.2, D12.2, D14.1, D15.1, J_FAN1.2, U6.2, U7.2
unnamed: A1.3, J_PaP-R1.2
unnamed: A1.4, J_PaP-R1.1
unnamed: A1.5, J_PaP-R1.3
unnamed: A1.6, J_PaP-R1.4
unnamed: A2.3, J_PaP-L1.2
unnamed: A2.4, J_PaP-L1.1
unnamed: A2.5, J_PaP-L1.3
unnamed: A2.6, J_PaP-L1.4
unnamed: D9.2, R2.1
unnamed: D13.2, R3.1
unnamed: D14.2, R4.1
unnamed: D15.2, R5.1
unnamed: D16.2, R10.1
unnamed: D17.2, R11.1
unnamed: J_DC_EXT1.1, U4.11
unnamed: J_DC_EXT1.2, U4.14
unnamed: J_DC_INT1.1, U4.3
unnamed: J_DC_INT1.2, U4.6
unnamed: J_FC_LB1.2, U1.15
unnamed: J_FC_LT1.2, U1.17
unnamed: J_FC_RB1.2, U1.14
unnamed: J_FC_RT1.2, U1.16
unnamed: J_SENSOR_AR1.2, U1.12
unnamed: J_SENSOR_AV1.2, U1.13
unnamed: R1.1, U3.31
unnamed: R1.2, SW1.2
unnamed: R2.2, U3.21
unnamed: R6.1, R8.2, U8.1
unnamed: R7.1, R9.2, U9.1
